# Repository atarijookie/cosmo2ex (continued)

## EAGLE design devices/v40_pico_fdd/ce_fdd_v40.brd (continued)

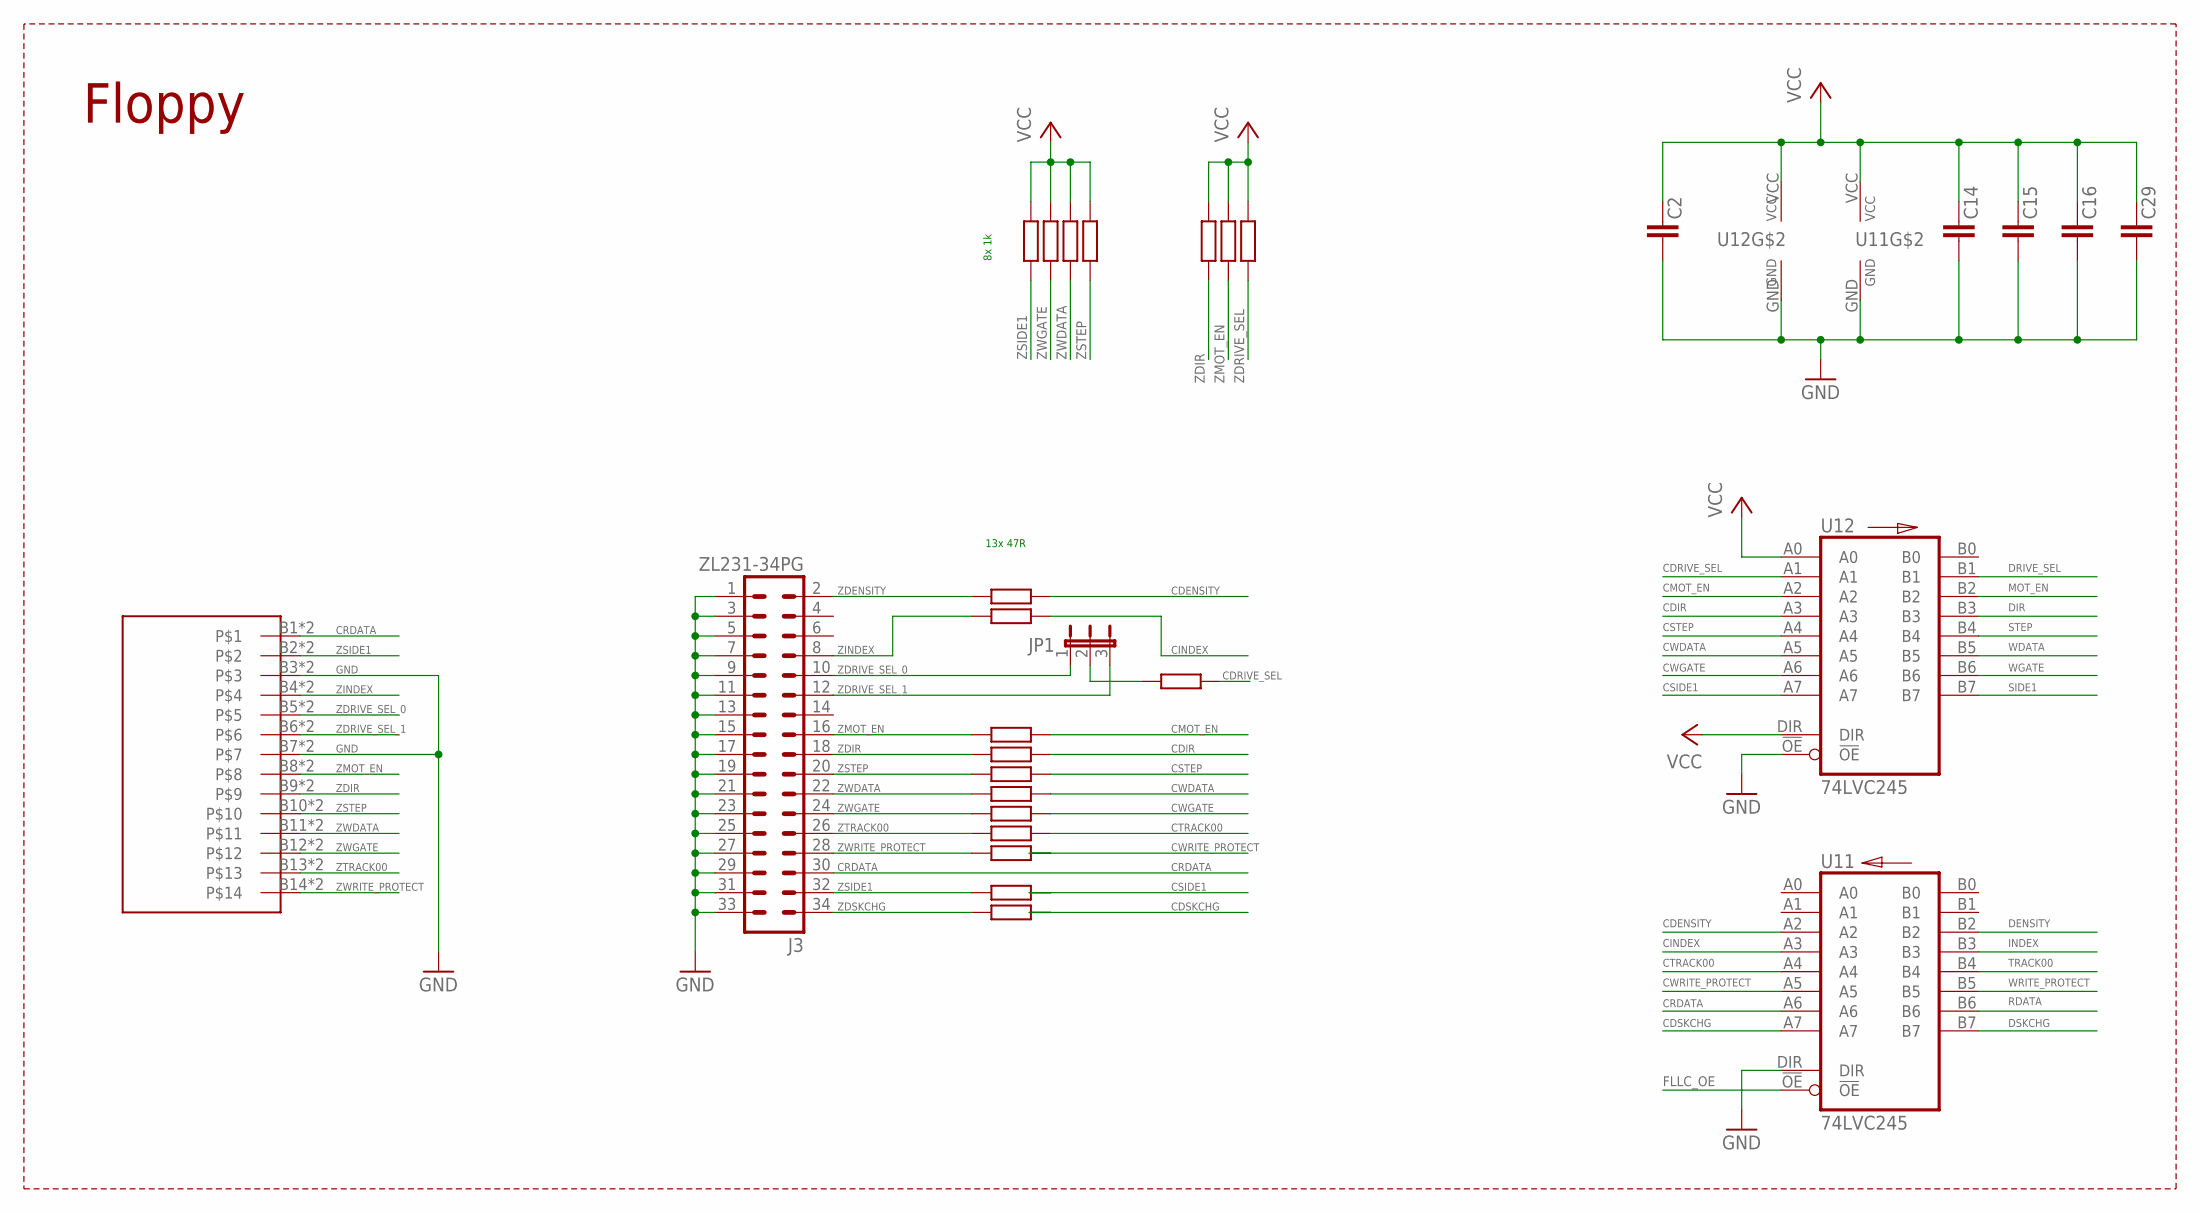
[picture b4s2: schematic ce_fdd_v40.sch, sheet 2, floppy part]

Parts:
C2, C14, C15, C16, C29: 100 nF; C0603
J3: ZL231-34PG; ML34
JP1: JP2E; JP2
R2, R3, R4, R6, R7, R8, R9, R10, R11, R12, R13, R15: 47R; R0603
R22, R23, R24, R26, R27, R28, R29: 1k; R0603
U11, U12: 74LVC245; 74LVC245_TSSOP20
U$1: DIN14

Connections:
CDENSITY: R2.1, U11.A2
CDIR: R7.1, U12.A3
CDRIVE_SEL: R4.1, U12.A1
CDSKCHG: R15.1, U11.A7
CINDEX: R3.1, U11.A3
CMOT_EN: R6.1, U12.A2
CRDATA: J3.30, U11.A6, U$1.B1, U$1.T1
CSIDE1: R13.1, U12.A7
CSTEP: R8.1, U12.A4
CTRACK00: R11.1, U11.A4
CWDATA: R9.1, U12.A5
CWGATE: R10.1, U12.A6
CWRITE_PROTECT: R12.1, U11.A5
DENSITY: U11.B2; also elsewhere on the board
DIR: U12.B3; also elsewhere on the board
DRIVE_SEL: U12.B1; also elsewhere on the board
DSKCHG: U11.B7; also elsewhere on the board
FLLC_OE: U11.!OE; also elsewhere on the board
GND: C2.2, C14.2, C15.2, C16.2, C29.2, J3.1, J3.3, J3.5, J3.7, J3.9, J3.11, J3.13, J3.15, J3.17, J3.19, J3.21, J3.23, J3.25, J3.27, J3.29, J3.31, J3.33, U11.DIR, U11.GND, U12.!OE, U12.GND, U$1.B3, U$1.B7, U$1.T3, U$1.T7; also elsewhere on the board
INDEX: U11.B3; also elsewhere on the board
MOT_EN: U12.B2; also elsewhere on the board
RDATA: U11.B6; also elsewhere on the board
SIDE1: U12.B7; also elsewhere on the board
STEP: U12.B4; also elsewhere on the board
TRACK00: U11.B4; also elsewhere on the board
VCC: C2.1, C14.1, C15.1, C16.1, C29.1, R22.1, R23.1, R24.1, R26.1, R27.1, R28.1, R29.1, U11.VCC, U12.A0, U12.DIR, U12.VCC; also elsewhere on the board
WDATA: U12.B5; also elsewhere on the board
WGATE: U12.B6; also elsewhere on the board
WRITE_PROTECT: U11.B5; also elsewhere on the board
ZDENSITY: J3.2, R2.2
ZDIR: J3.18, R7.2, R27.2, U$1.B9, U$1.T9
ZDRIVE_SEL: JP1.2, R4.2, R29.2
ZDRIVE_SEL_0: J3.10, JP1.1, U$1.B5, U$1.T5
ZDRIVE_SEL_1: J3.12, JP1.3, U$1.B6, U$1.T6
ZDSKCHG: J3.34, R15.2
ZINDEX: J3.8, R3.2, U$1.B4, U$1.T4
ZMOT_EN: J3.16, R6.2, R28.2, U$1.B8, U$1.T8
ZSIDE1: J3.32, R13.2, R22.2, U$1.B2, U$1.T2
ZSTEP: J3.20, R8.2, R26.2, U$1.B10, U$1.T10
ZTRACK00: J3.26, R11.2, U$1.B13, U$1.T13
ZWDATA: J3.22, R9.2, R24.2, U$1.B11, U$1.T11
ZWGATE: J3.24, R10.2, R23.2, U$1.B12, U$1.T12
ZWRITE_PROTECT: J3.28, R12.2, U$1.B14, U$1.T14

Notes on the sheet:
Floppy
13x 47R
8x 1k

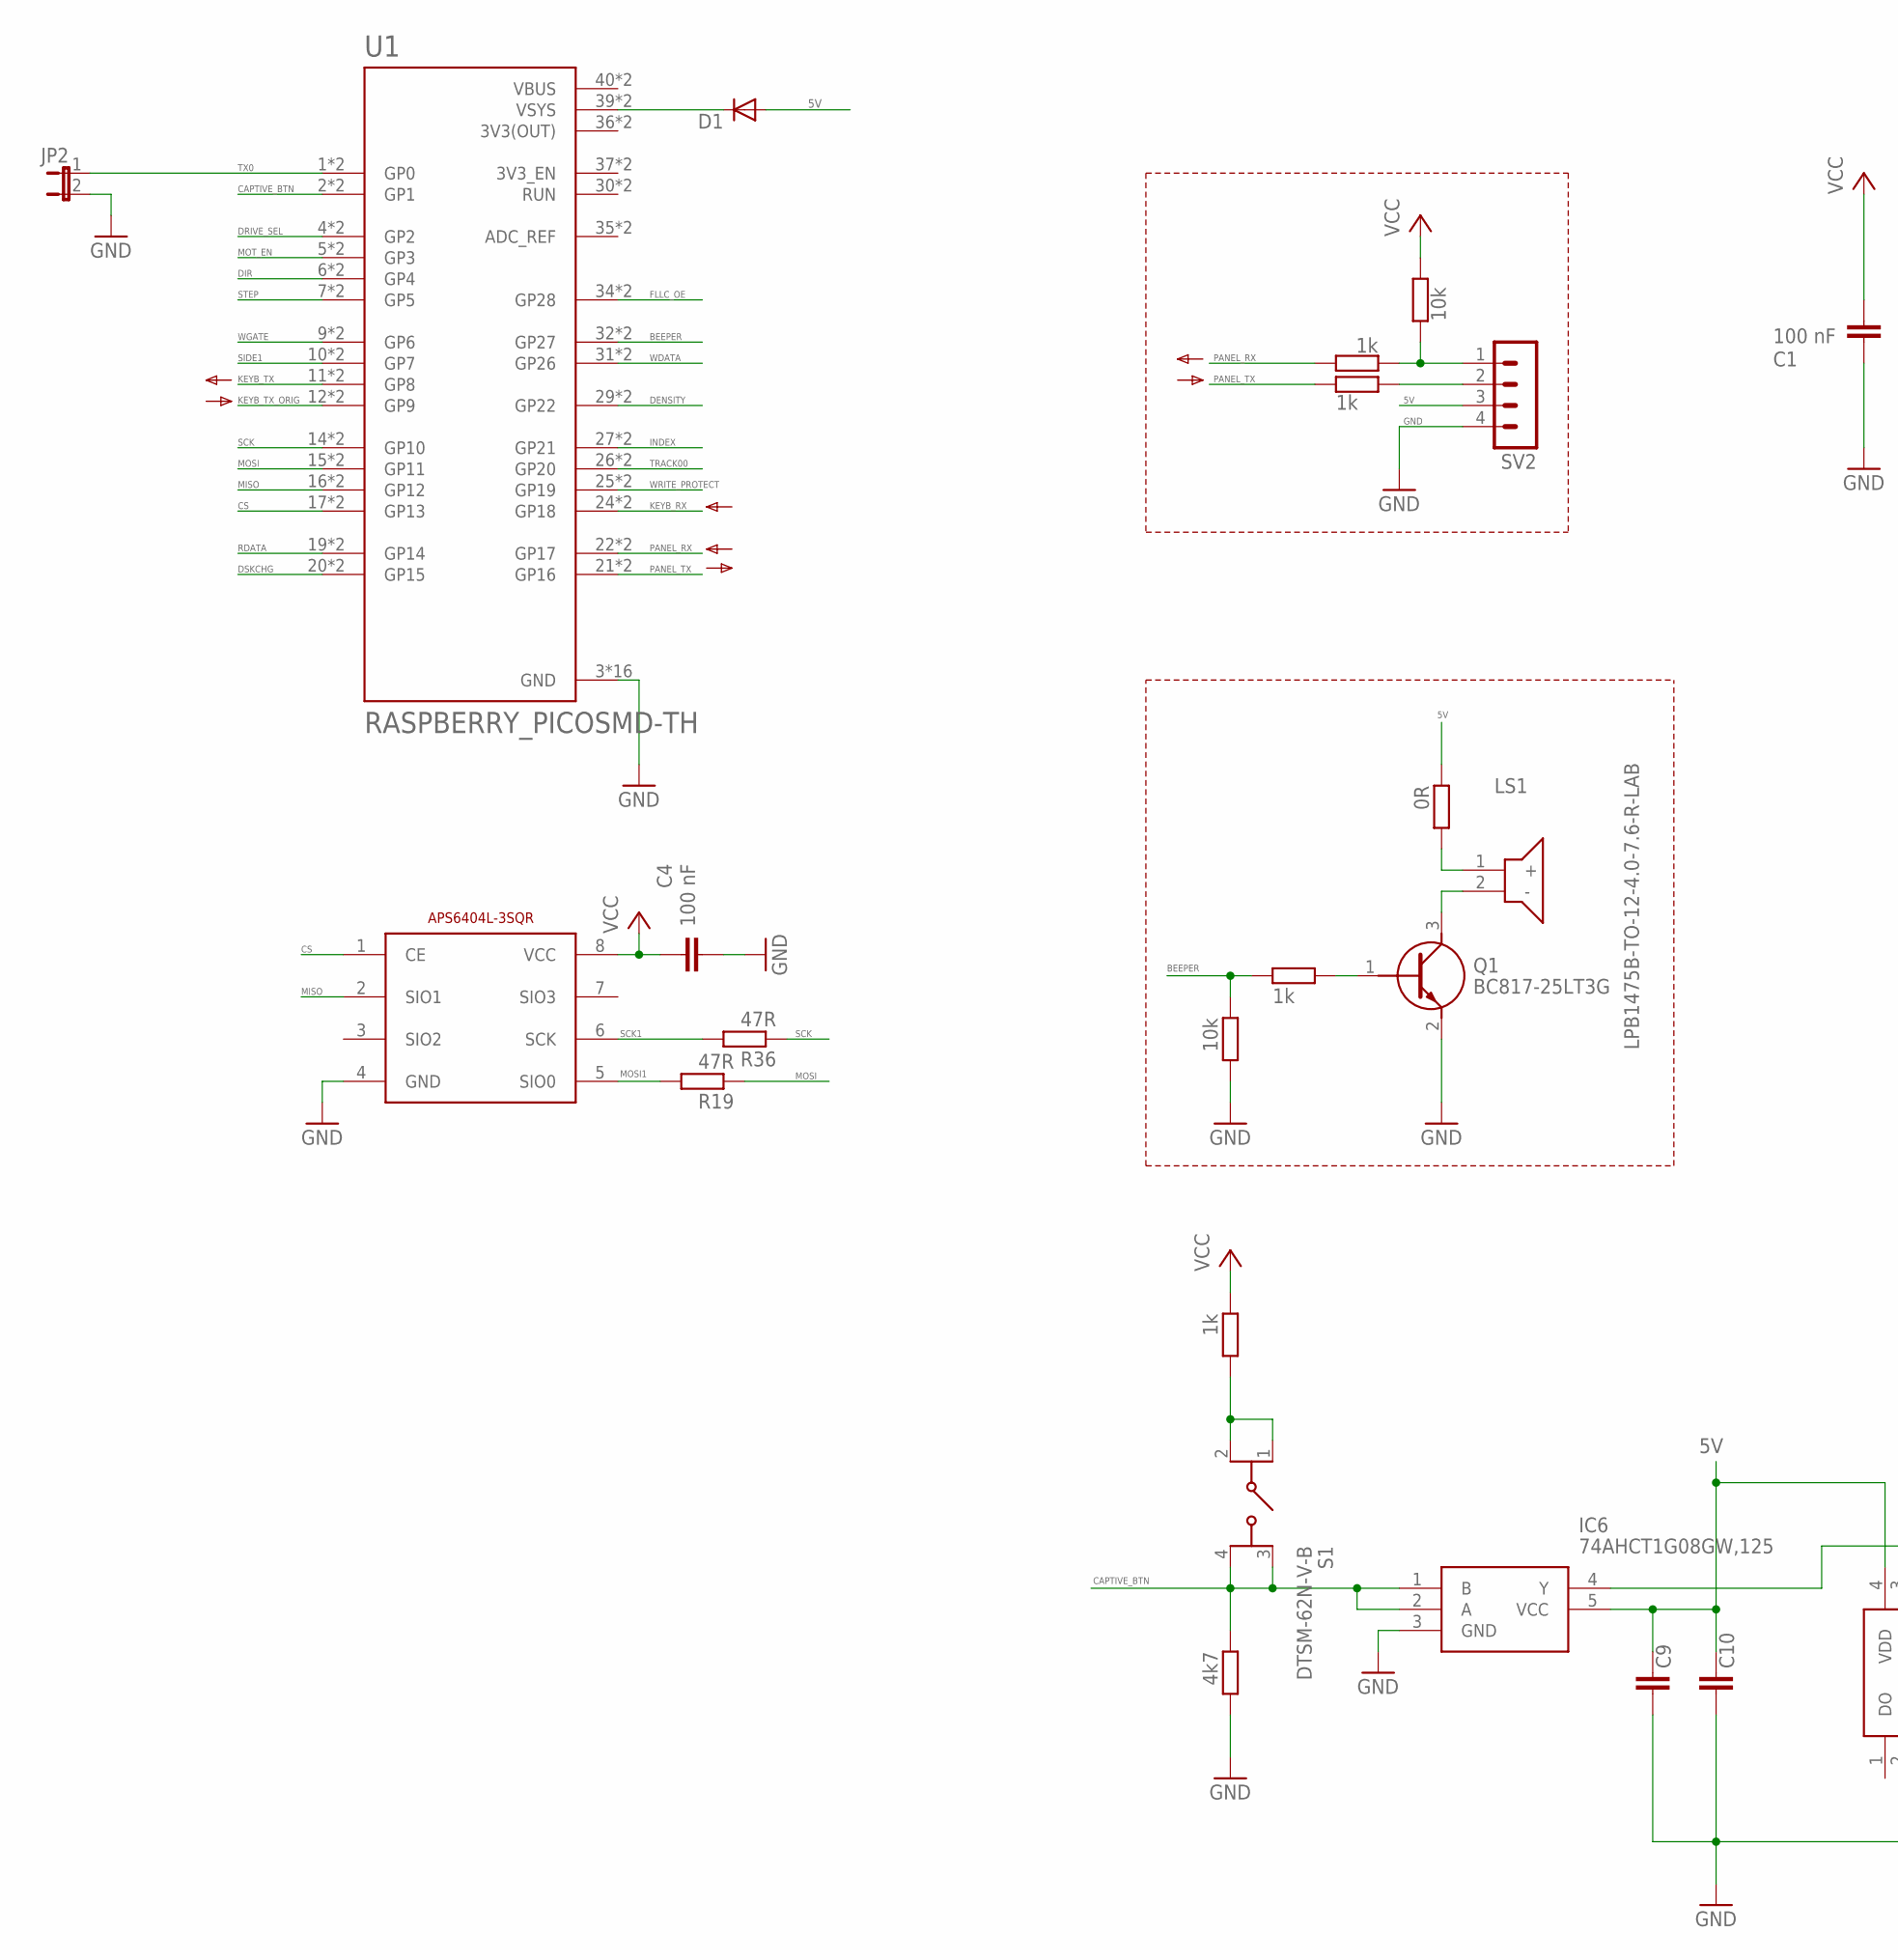
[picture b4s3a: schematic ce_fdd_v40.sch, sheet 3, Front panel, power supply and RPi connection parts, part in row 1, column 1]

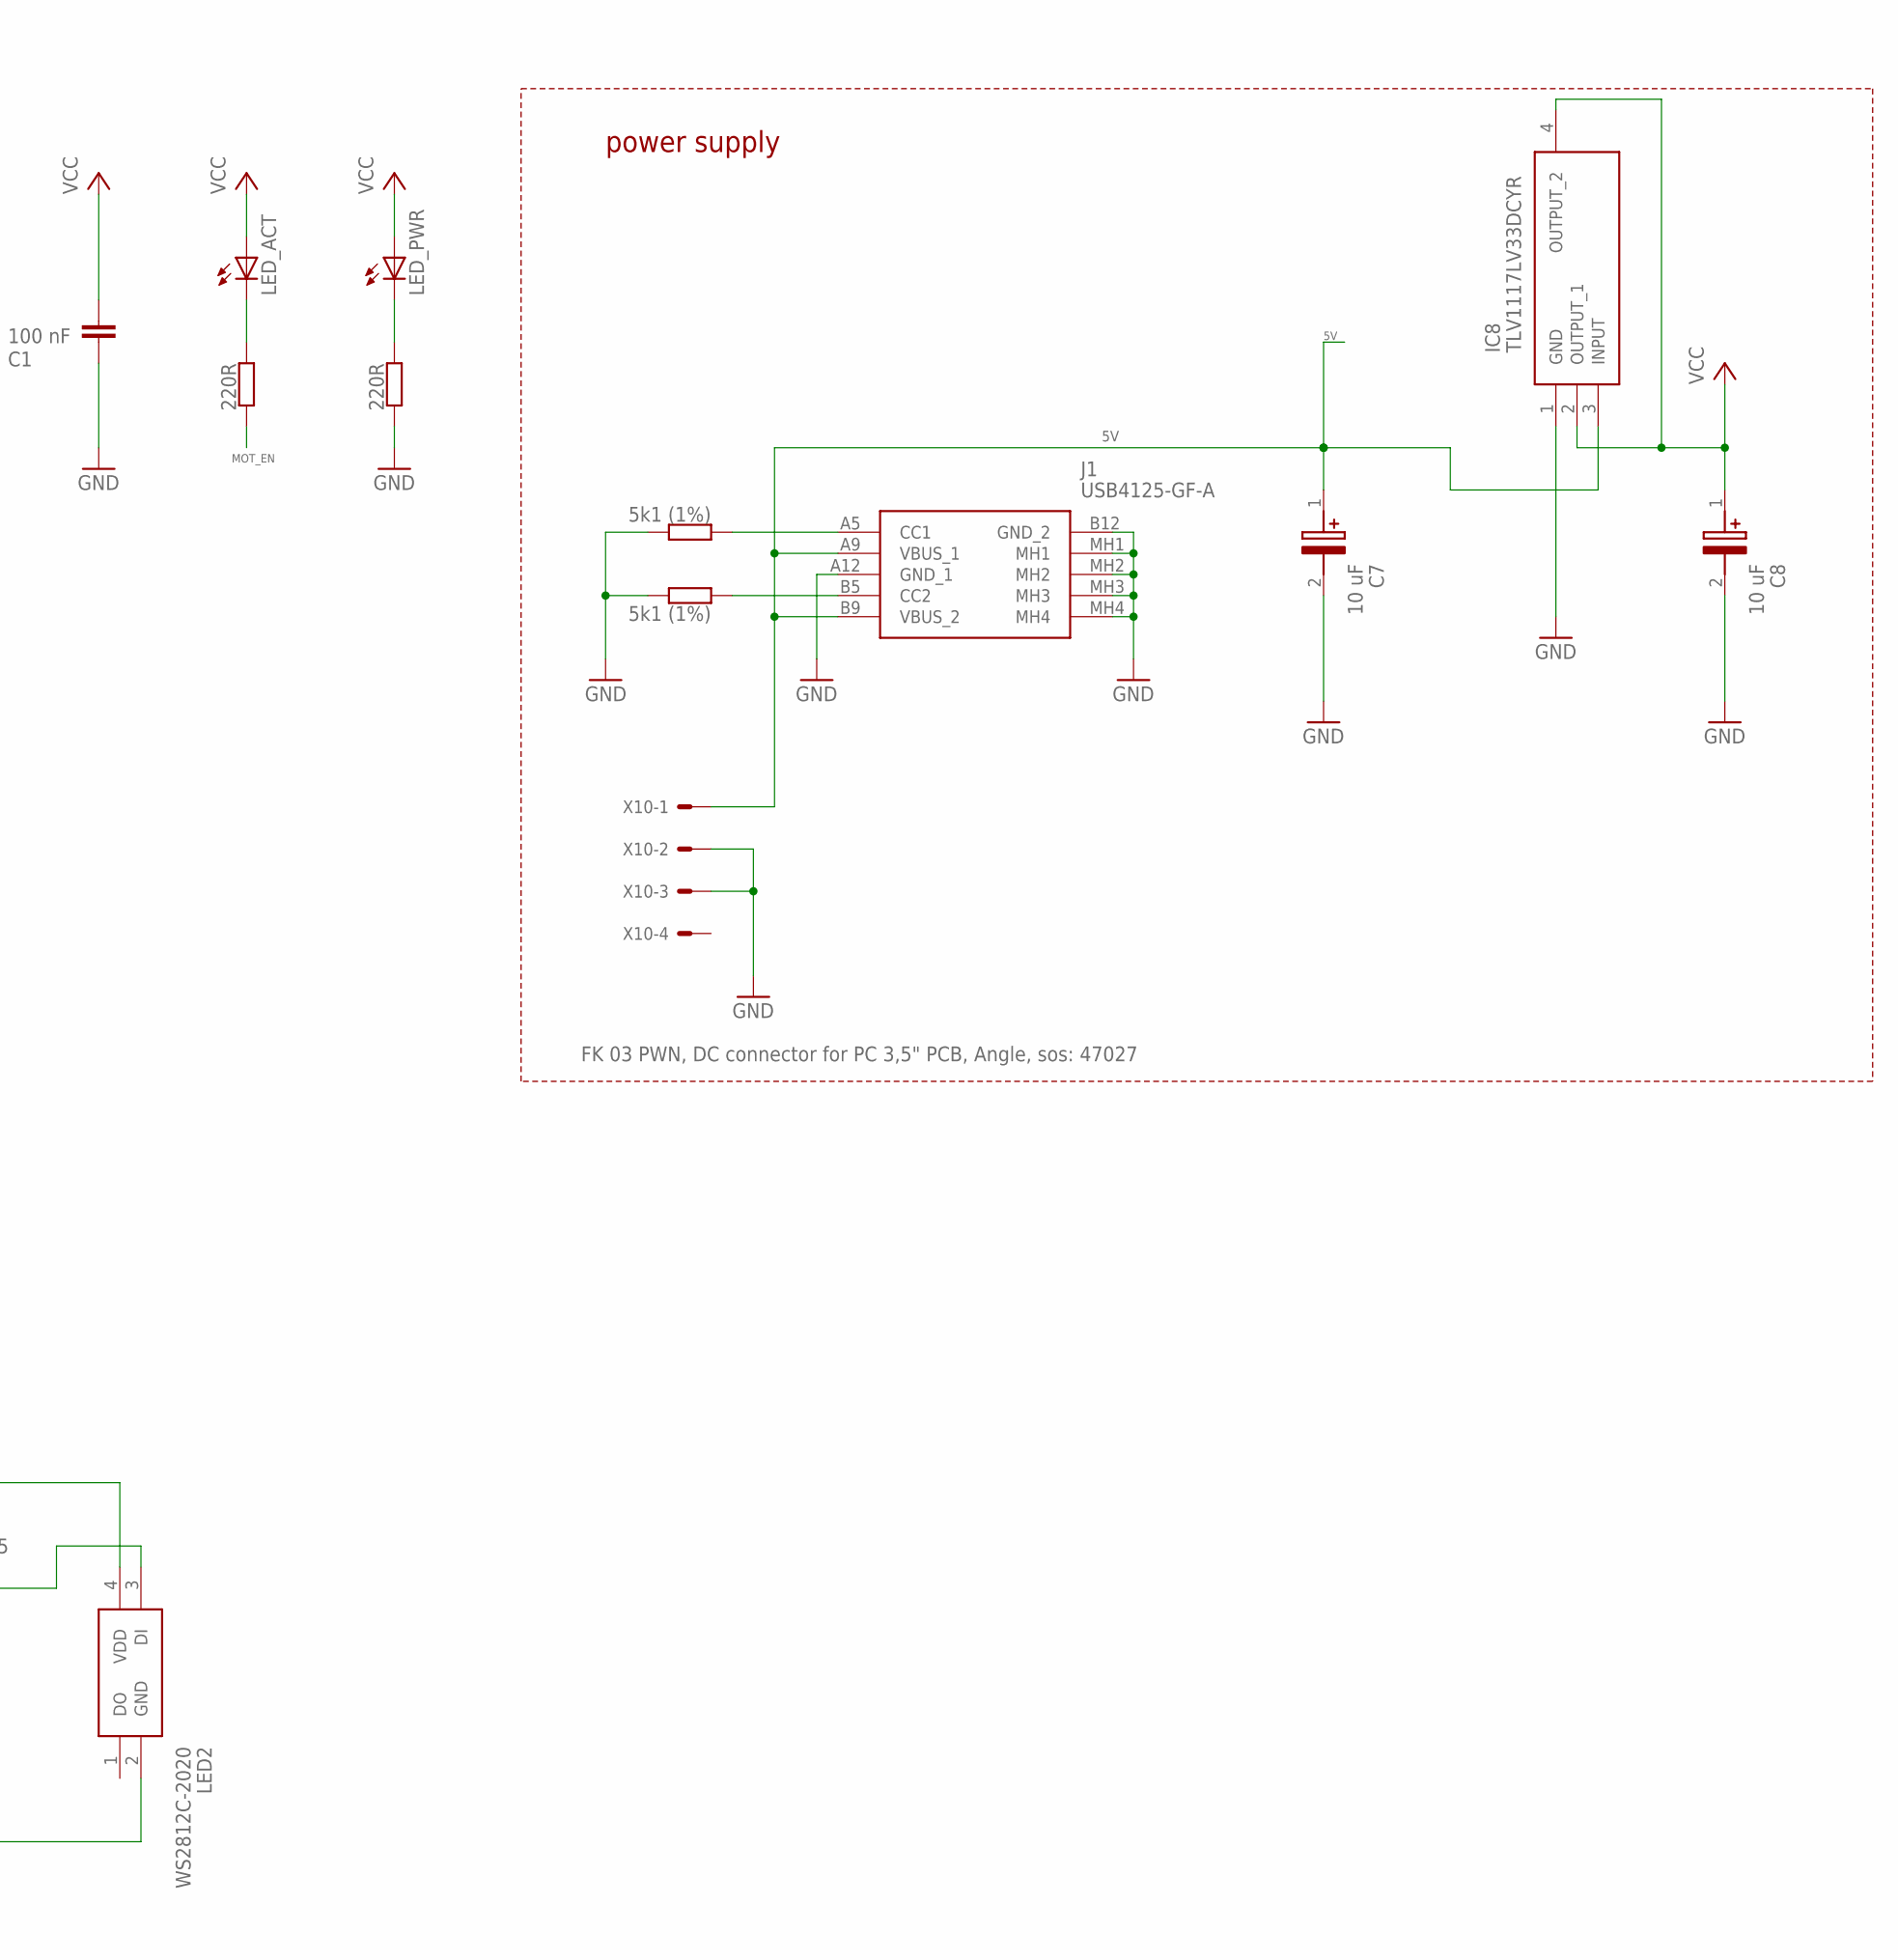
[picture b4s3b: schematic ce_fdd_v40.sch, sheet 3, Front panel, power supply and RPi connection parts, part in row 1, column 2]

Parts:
C1, C4, C9, C10: 100 nF; C0603
C7, C8: 10 uF; CAPPM3528X210N
D1: SK110-DIO; DO214AC
IC6: 74AHCT1G08GW,125; SOT65P212X110-5N
IC8: TLV1117LV33DCYR; SOT230P700X180-4N
J1: USB4125-GF-A; USB4125GFA
JP2: JP1E; JP1
LED2: WS2812C-2020; WS2812C2020
LED_ACT: LEDSML0603; SML0603
LED_PWR: LEDSML0603; SML0603
LS1: LPB1475B-TO-12-4.0-7.6-R-LAB; LPB1475BTO124076RLAB
Q1: BC817-25LT3G; SOT96P237X111-3N
R5: 0R; R0603
R14, R17: 5k1 (1%); R0603
R18, R35: 220R; R0603
R19, R36: 47R; R0603
R20, R30, R32, R37: 1k; R0603
R21, R31: 10k; R0603
R38: 4k7; R0603
S1: DTSM-62N-V-B; DTSM62NVB
SV2: MA04-1
U1: RASPBERRY_PICOSMD-TH; PICO-PKG
U$2: APS6404L-3SQR; SOP-8L
X10: FK 03 PWN, DC connector for PC 3,5" PCB, Angle, s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; 7395-04

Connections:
3V3(OUT): U1.36 (3V3(OUT)), U1.P$36 (3V3(OUT))
5V: C7.1 (+), C9.1, C10.1, D1.A, IC6.5 (VCC), IC8.3 (INPUT), J1.A9 (VBUS_1), J1.B9 (VBUS_2), LED2.4 (VDD), R5.1, SV2.3, X10.1; also elsewhere on the board
BEEPER: R30.1, R31.1, U1.32 (GP27), U1.P$32 (GP27)
CAPTIVE_BTN: IC6.1 (B), IC6.2 (A), R38.1, S1.3 (NO_1), S1.4 (NO_2), U1.2 (GP1), U1.P$2 (GP1)
CS: U1.17 (GP13), U1.P$17 (GP13), U$2.1 (CE)
DENSITY: U1.29 (GP22), U1.P$29 (GP22); also elsewhere on the board
DIR: U1.6 (GP4), U1.P$6 (GP4); also elsewhere on the board
DRIVE_SEL: U1.4 (GP2), U1.P$4 (GP2); also elsewhere on the board
DSKCHG: U1.20 (GP15), U1.P$20 (GP15); also elsewhere on the board
FLLC_OE: U1.34 (GP28), U1.P$34 (GP28); also elsewhere on the board
GND: C1.2, C4.1, C7.2 (-), C8.2 (-), C9.2, C10.2, IC6.3 (GND), IC8.1 (GND), J1.A12 (GND_1), J1.B12 (GND_2), J1.MH1, J1.MH2, J1.MH3, J1.MH4, JP2.2, LED2.2 (GND), Q1.2 (E), R14.2, R17.2, R18.2, R31.2, R38.2, SV2.4, U1.3 (GND), U1.8 (GND), U1.13 (GND), U1.18 (GND), U1.23 (GND), U1.28 (GND), U1.33 (GND), U1.38 (GND), U1.P$3 (GND), U1.P$8 (GND), U1.P$13 (GND), U1.P$18 (GND), U1.P$23 (GND), U1.P$28 (GND), U1.P$33 (GND), U1.P$38 (GND), U$2.4 (GND), X10.2, X10.3; also elsewhere on the board
INDEX: U1.27 (GP21), U1.P$27 (GP21); also elsewhere on the board
KEYB_RX: U1.24 (GP18), U1.P$24 (GP18); also elsewhere on the board
KEYB_TX: U1.11 (GP8), U1.P$11 (GP8); also elsewhere on the board
KEYB_TX_ORIG: U1.12 (GP9), U1.P$12 (GP9); also elsewhere on the board
MISO: U1.16 (GP12), U1.P$16 (GP12), U$2.2 (SIO1)
MOSI: R19.1, U1.15 (GP11), U1.P$15 (GP11)
MOSI1: R19.2, U$2.5 (SIO0)
MOT_EN: R35.2, U1.5 (GP3), U1.P$5 (GP3); also elsewhere on the board
unnamed: J1.B5 (CC2), R14.1
unnamed: J1.A5 (CC1), R17.1
unnamed: Q1.1 (B), R30.2
unnamed: LS1.2 (-), Q1.3 (C)
unnamed: LED_ACT.C, R35.1
unnamed: LED_PWR.C, R18.1
unnamed: LS1.1 (+), R5.2
unnamed: R21.1, R32.1, SV2.1
unnamed: R37.2, SV2.2
unnamed: R20.2, S1.1 (COM_1), S1.2 (COM_2)
unnamed: IC6.4 (Y), LED2.3 (DI)
unnamed: D1.C, U1.39 (VSYS), U1.P$39 (VSYS)
PANEL_RX: R32.2, U1.22 (GP17), U1.P$22 (GP17)
PANEL_TX: R37.1, U1.21 (GP16), U1.P$21 (GP16)
RDATA: U1.19 (GP14), U1.P$19 (GP14); also elsewhere on the board
SCK: R36.1, U1.14 (GP10), U1.P$14 (GP10)
SCK1: R36.2, U$2.6 (SCK)
SIDE1: U1.10 (GP7), U1.P$10 (GP7); also elsewhere on the board
STEP: U1.7 (GP5), U1.P$7 (GP5); also elsewhere on the board
TRACK00: U1.26 (GP20), U1.P$26 (GP20); also elsewhere on the board
TX0: JP2.1, U1.1 (GP0), U1.P$1 (GP0)
VBUS: U1.40 (VBUS), U1.P$40 (VBUS)
VCC: C1.1, C4.2, C8.1 (+), IC8.2 (OUTPUT_1), IC8.4 (OUTPUT_2), LED_ACT.A, LED_PWR.A, R20.1, R21.2, U$2.8 (VCC); also elsewhere on the board
WDATA: U1.31 (GP26), U1.P$31 (GP26); also elsewhere on the board
WGATE: U1.9 (GP6), U1.P$9 (GP6); also elsewhere on the board
WRITE_PROTECT: U1.25 (GP19), U1.P$25 (GP19); also elsewhere on the board

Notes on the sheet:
power supply

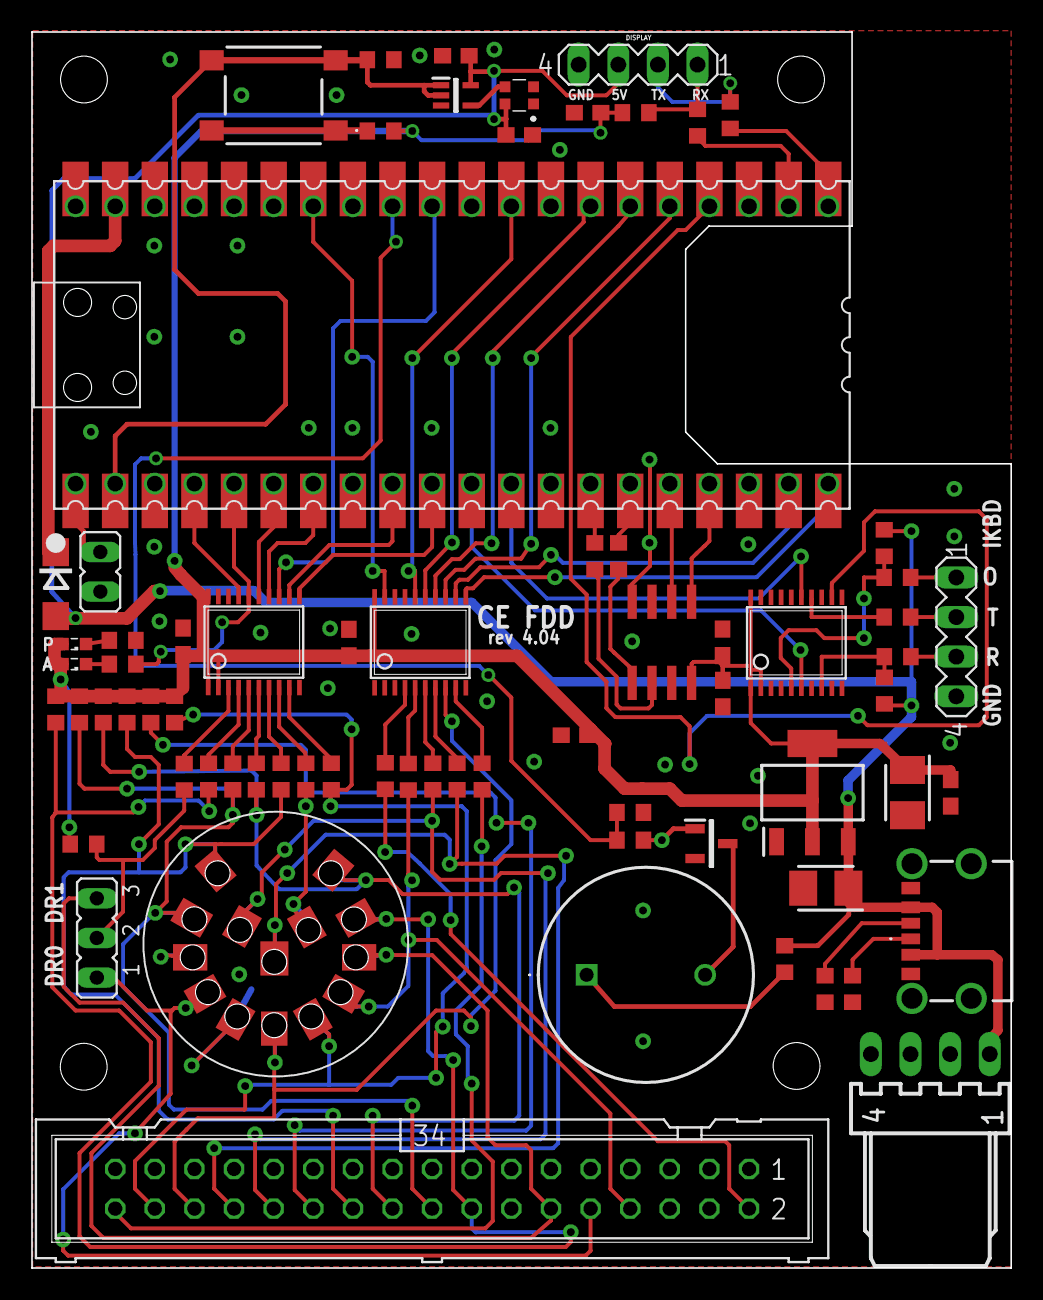
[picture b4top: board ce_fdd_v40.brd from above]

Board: 2 copper layers, 62.8 x 79.2 mm, 71 parts (0 on the bottom side), 78 nets.

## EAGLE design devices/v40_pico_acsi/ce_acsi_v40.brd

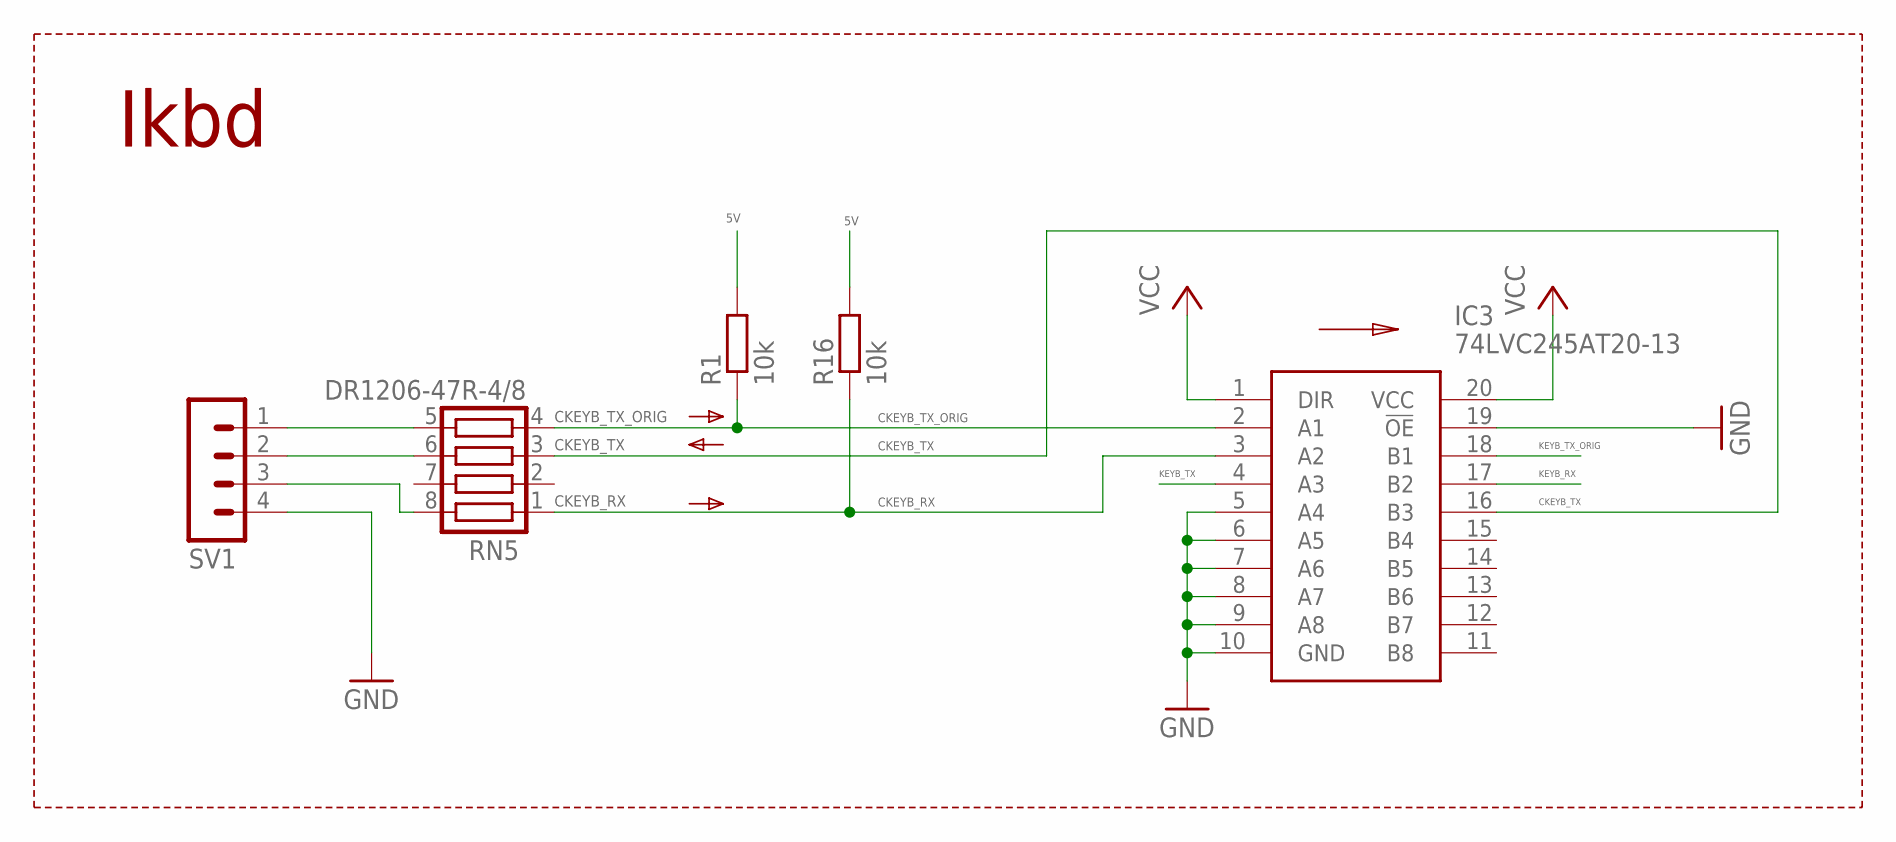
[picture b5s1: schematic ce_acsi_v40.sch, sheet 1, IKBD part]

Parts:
IC3: 74LVC245AT20-13; SOP65P640X120-20N
R1, R16: 10k; R0603
RN5: DR1206-47R-4/8; CTS742C083
SV1: MA04-1

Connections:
5V: R1.2, R16.2; also elsewhere on the board
CKEYB_RX: IC3.3 (A2), R16.1, RN5.1
CKEYB_TX: IC3.16 (B3), RN5.3
CKEYB_TX_ORIG: IC3.2 (A1), R1.1, RN5.4
GND: IC3.5 (A4), IC3.6 (A5), IC3.7 (A6), IC3.8 (A7), IC3.9 (A8), IC3.10 (GND), IC3.19 (!OE), SV1.4; also elsewhere on the board
KEYB_RX: IC3.17 (B2); also elsewhere on the board
KEYB_TX: IC3.4 (A3); also elsewhere on the board
KEYB_TX_ORIG: IC3.18 (B1); also elsewhere on the board
unnamed: RN5.6, SV1.2
VCC: IC3.1 (DIR), IC3.20 (VCC); also elsewhere on the board
ZKEYB_RX: RN5.8, SV1.3
ZKEYB_TX_ORIG: RN5.5, SV1.1

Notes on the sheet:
Ikbd
